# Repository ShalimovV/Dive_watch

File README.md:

# Dive_watch
DIY dive computer project for free diving

KiCAD project - https://github.com/ShalimovV/Dive_watch/tree/main/Hardware/d_watch_v2

Source code are here - https://github.com/ShalimovV/d_watch_v2_wb55

Youtube - https://www.youtube.com/@ShalimovProjects

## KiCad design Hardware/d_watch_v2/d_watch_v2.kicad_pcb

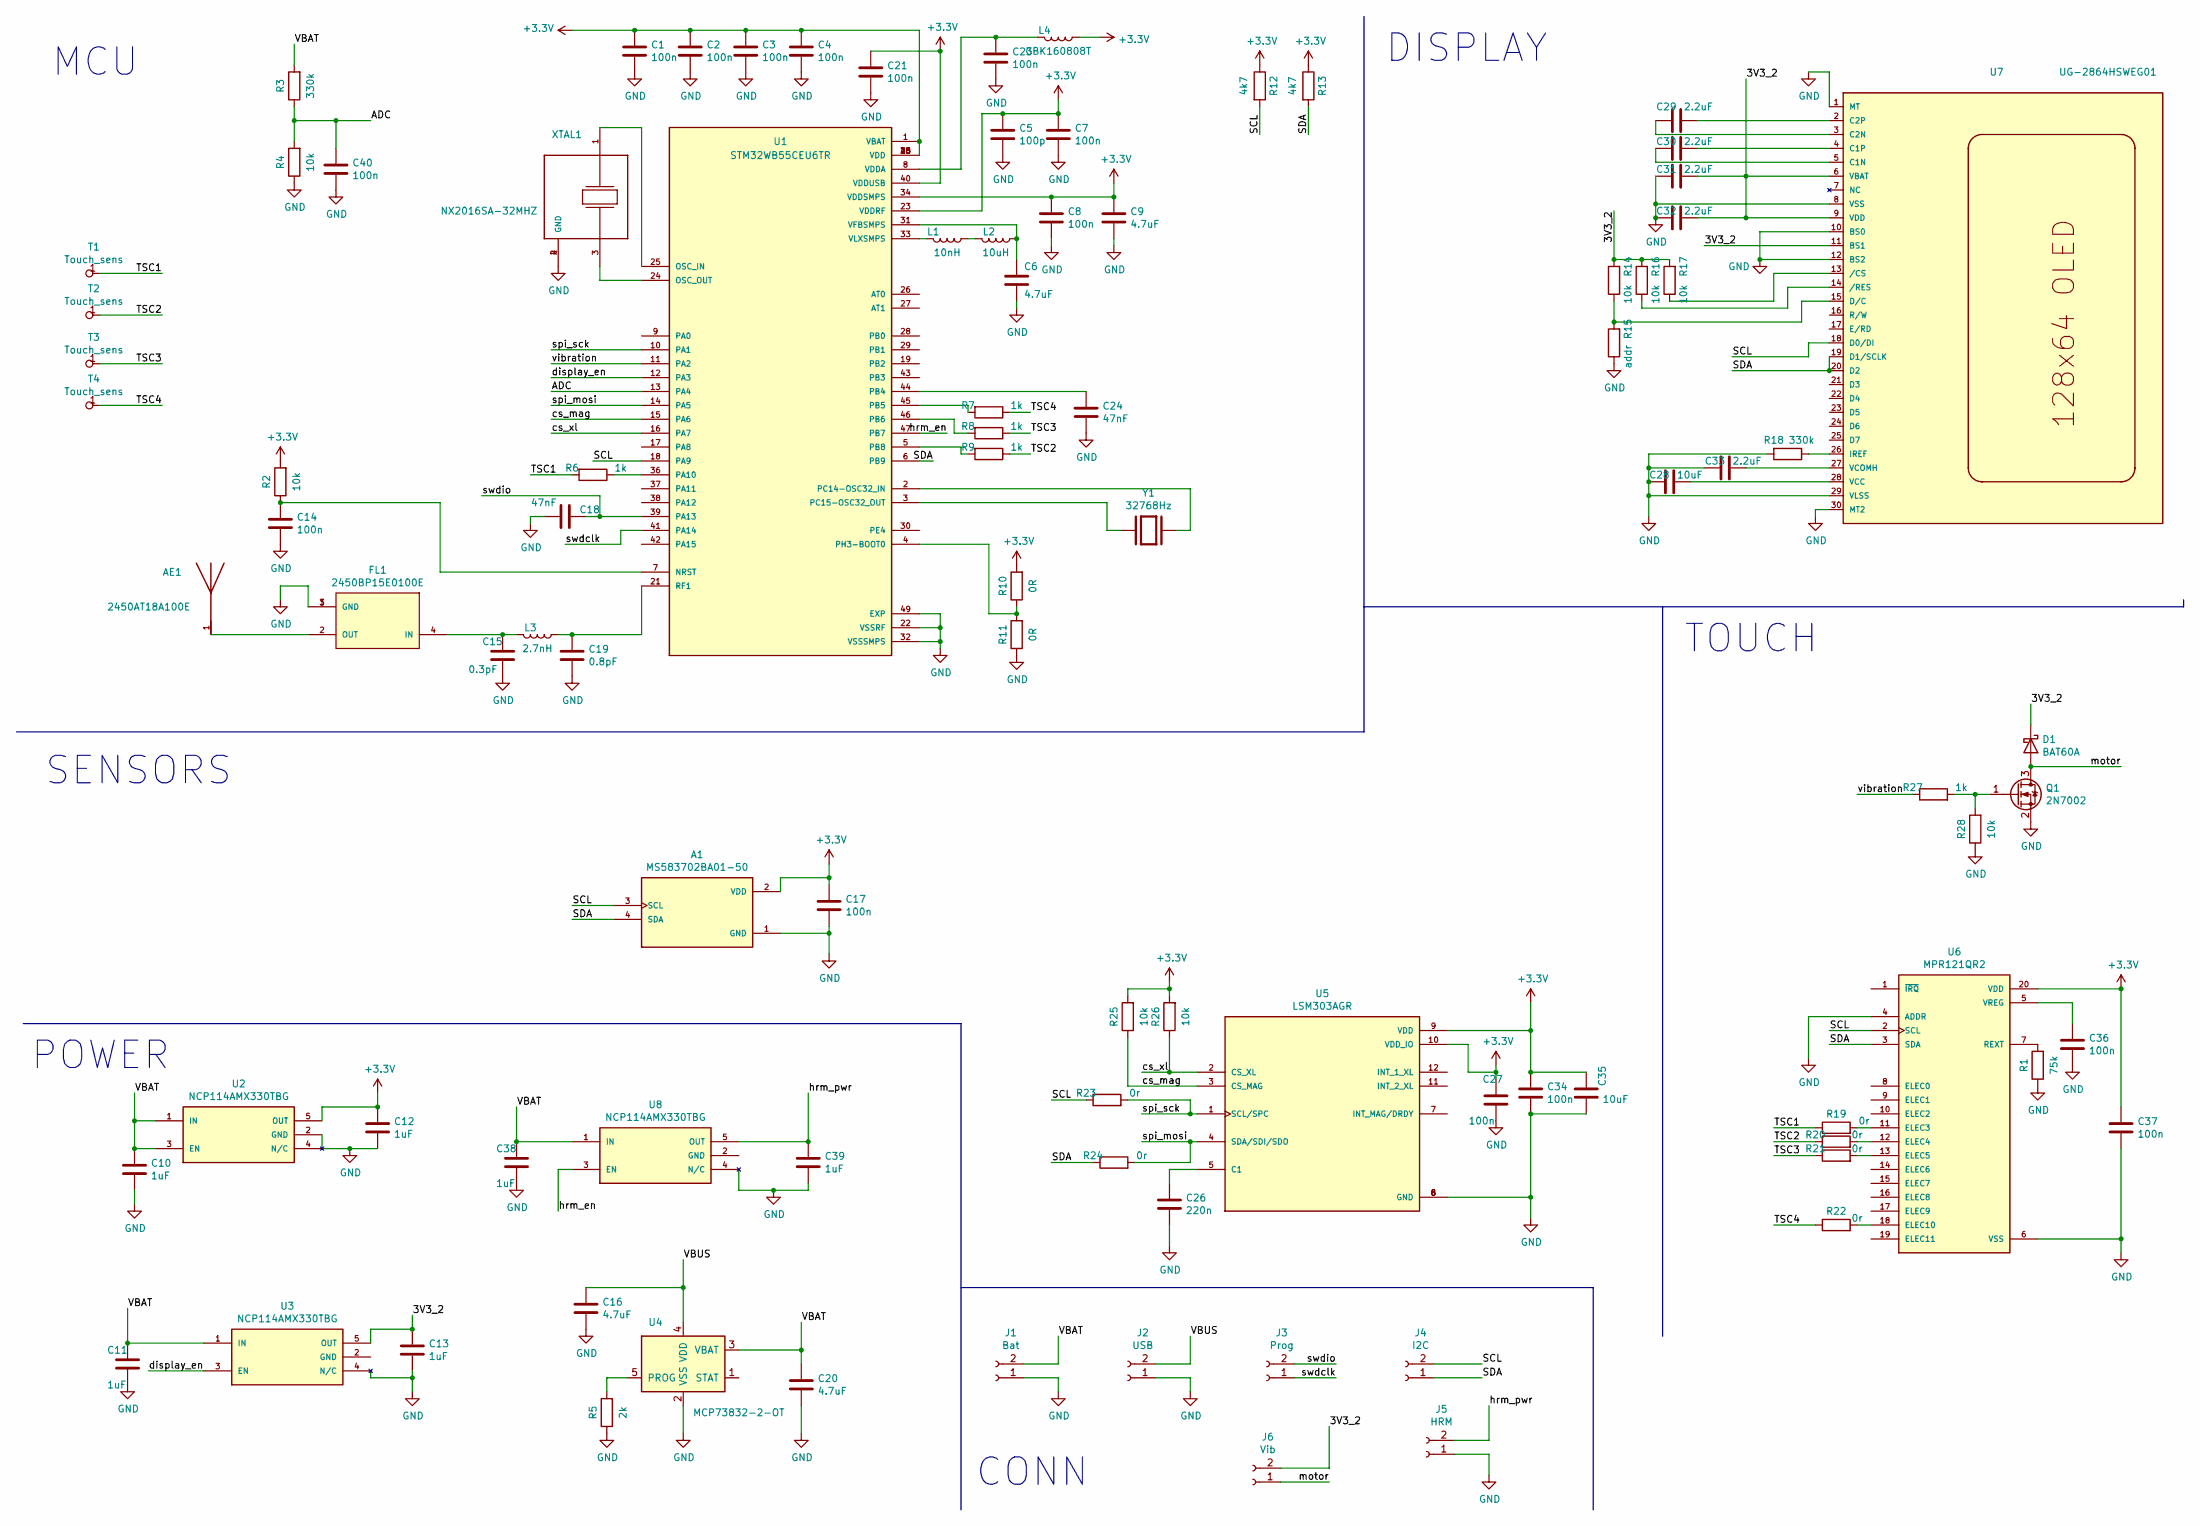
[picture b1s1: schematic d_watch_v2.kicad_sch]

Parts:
A1: MS583702BA01-50; XDCR_MS583702BA01-50
AE1: 2450AT18A100E; ANTC3216X140N; PARTREV 1.3
C1, C2, C3, C4, C7, C8, C14, C17, C21, C23, C27, C34, C36, C37, C40: 100n; C_0603_1608Metric
C5: 100p; C_0603_1608Metric
C6, C9, C16, C20: 4.7uF; C_0603_1608Metric
C10, C11, C12, C13, C38, C39: 1uF; C_0603_1608Metric
C15: 0.3pF; C_0603_1608Metric
C18, C24: 47nF; C_0603_1608Metric
C19: 0.8pF; C_0603_1608Metric
C26: 220n; C_0603_1608Metric
C28, C35: 10uF; C_0603_1608Metric
C29, C30, C31, C32, C33: 2.2uF; C_0603_1608Metric
D1: BAT60A; D_SOD-323
FL1: 2450BP15E0100E; FIL_2450BP15E0100E; PARTREV 1.0
J1: Bat; PinHeader_1x02_P2.54mm_Vertical
J2: USB; PinHeader_1x02_P2.54mm_Vertical
J3: Prog; PinHeader_1x02_P2.54mm_Vertical
J4: I2C; PinHeader_1x02_P2.54mm_Vertical
J5: HRM; PinHeader_1x02_P2.54mm_Vertical
J6: Vib; PinHeader_1x02_P1.00mm_Vertical
L1: 10nH; L_0603_1608Metric
L2: 10uH; L_0603_1608Metric
L3: 2.7nH; L_0603_1608Metric
L4: GBK160808T; L_0603_1608Metric
Q1: 2N7002; SOT-23
R1: 75k; R_0603_1608Metric
R2, R4, R14, R16, R17, R25, R26, R28: 10k; R_0603_1608Metric
R3, R18: 330k; R_0603_1608Metric
R5: 2k; R_0603_1608Metric
R6, R7, R8, R9, R27: 1k; R_0603_1608Metric
R10, R11: 0R; R_0603_1608Metric
R12, R13: 4k7; R_0603_1608Metric
R15: addr; R_0603_1608Metric
R19, R20, R21, R22, R23, R24: 0r; R_0603_1608Metric
T1, T2, T3, T4: Touch_sens; touch_pad
U1: STM32WB55CEU6TR; QFN-48-1EP_7x7mm_P0.5mm_EP5.45x5.45mm; PARTREV 5
U2, U3, U8: NCP114AMX330TBG; SOT-23-5
U4: MCP73832-2-OT; SOT-23-5
U5: LSM303AGR; LGA-12_2x2mm_P0.5mm
U6: MPR121QR2; QFN40P300X300X60-20N
U7: UG-2864HSWEG01; 1X30-0.7MM
XTAL1: NX2016SA-32MHZ; OSCCC200X160X50N; PARTREV N/A
Y1: 32768Hz; XTAL_12.87150; PARTREV 22.06.2021

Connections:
+3V3: A1.2 (VDD), C1.1, C2.1, C3.1, C4.1, C5.1, C7.1, C8.1, C9.1, C12.1, C17.1, C21.1, C27.1, C34.1, C35.1, C37.1, L4.1, R2.2, R10.2, R12.1, R13.1, R25.2, R26.2, U1.1 (VBAT), U1.20 (VDD), U1.23 (VDDRF), U1.34 (VDDSMPS), U1.35 (VDD), U1.40 (VDDUSB), U1.48 (VDD), U2.5 (OUT), U5.9 (VDD), U5.10 (VDD_IO), U6.20 (VDD)
/3V3_2: C13.1, C31.1, C32.1, D1.1 (K), J6.2, R14.2, R16.2, R17.2, U3.5 (OUT), U7.6 (VBAT), U7.9 (VDD), U7.11 (BS1)
/ADC: C40.1, R3.1, R4.2, U1.13 (PA4)
/SCL: A1.3 (SCL), J4.2, R12.2, R23.1, U1.18 (PA9), U6.2 (SCL), U7.18 (D0/DI)
/SDA: A1.4 (SDA), J4.1, R13.2, R24.1, U1.6 (PB9), U6.3 (SDA), U7.19 (D1/SCLK), U7.20 (D2)
/TSC1: R6.2, R19.1, T1.1
/TSC2: R9.1, R20.1, T2.1
/TSC3: R8.1, R21.1, T3.1
/TSC4: R7.1, R22.1, T4.1
/VBAT: C10.1, C11.1, C20.1, C38.1, J1.2, R3.2, U2.1 (IN), U2.3 (EN), U3.1 (IN), U4.3 (VBAT), U8.1 (IN)
/VBUS: C16.1, J2.2, U4.4 (VDD)
/cs_mag: R25.1, U1.15 (PA6), U5.3 (CS_MAG)
/cs_xl: R26.1, U1.16 (PA7), U5.2 (CS_XL)
/display_en: U1.12 (PA3), U3.3 (EN)
/hrm_en: U1.47 (PB7), U8.3 (EN)
/hrm_pwr: C39.1, J5.2, U8.5 (OUT)
/motor: D1.2 (A), J6.1, Q1.3 (D)
/spi_mosi: R24.2, U1.14 (PA5), U5.4 (SDA/SDI/SDO)
/spi_sck: R23.2, U1.10 (PA1), U5.1 (SCL/SPC)
/swdclk: J3.1, U1.41 (PA14)
/swdio: C18.1, J3.2, U1.39 (PA13)
/vibration: R27.1, U1.11 (PA2)
GND: A1.1 (GND), C1.2, C2.2, C3.2, C4.2, C5.2, C6.2, C7.2, C8.2, C9.2, C10.2, C11.2, C12.2, C13.2, C14.2, C15.2, C16.2, C17.2, C18.2, C19.2, C20.2, C21.2, C23.2, C24.2, C26.2, C27.2, C28.2, C31.2, C32.2, C33.2, C34.2, C35.2, C36.2, C37.2, C38.2, C39.2, C40.2, FL1.1 (GND), FL1.3 (GND), J1.1, J2.1, J5.1, Q1.2 (S), R1.1, R4.1, R5.1, R11.1, R15.1, R18.2, R28.1, U1.22 (VSSRF), U1.32 (VSSSMPS), U1.49 (EXP), U2.2 (GND), U2.4 (N/C), U3.4 (N/C), U4.2 (VSS), U5.6 (GND), U5.8 (GND), U6.4 (ADDR), U6.6 (VSS), U7.1 (MT), U7.8 (VSS), U7.10 (BS0), U7.12 (BS2), U7.29 (VLSS), U7.30 (MT2), U8.4 (N/C), XTAL1.2 (GND), XTAL1.4 (GND); also elsewhere on the board
unnamed: AE1.1, FL1.2 (OUT)
unnamed: C6.1, L2.1, U1.31 (VFBSMPS)
unnamed: C14.1, R2.1, U1.7 (NRST)
unnamed: C15.1, FL1.4 (IN), L3.2
unnamed: C19.1, L3.1, U1.21 (RF1)
unnamed 28: U1.3 (PC15-OSC32_OUT), Y1.1; also elsewhere on the board
unnamed: C23.1, L4.2, U1.8 (VDDA)
unnamed: C24.1, U1.44 (PB4)
unnamed 31: U1.2 (PC14-OSC32_IN), Y1.2; also elsewhere on the board
unnamed: C26.1, U5.5 (C1)
unnamed: C28.1, U7.28 (VCC)
unnamed: C29.1, U7.2 (C2P)
unnamed: C29.2, U7.3 (C2N)
unnamed: C30.1, U7.4 (C1P)
unnamed: C30.2, U7.5 (C1N)
unnamed: C33.1, U7.27 (VCOMH)
unnamed: C36.1, U6.5 (VREG)
unnamed: L1.1, L2.2
unnamed: L1.2, U1.33 (VLXSMPS)
unnamed: Q1.1 (G), R27.2, R28.2
unnamed: R1.2, U6.7 (REXT)
unnamed: R5.2, U4.5 (PROG)
unnamed: R6.1, U1.36 (PA10)
unnamed: R7.2, U1.45 (PB5)
unnamed: R8.2, U1.46 (PB6)
unnamed: R9.2, U1.5 (PB8)
unnamed: R10.1, R11.2, U1.4 (PH3-BOOT0)
unnamed: R14.1, R15.2, U7.15 (D/C)
unnamed: R16.1, U7.14 (/RES)
unnamed: R17.1, U7.13 (/CS)
unnamed: R18.1, U7.26 (IREF)
unnamed: R19.2, U6.11 (ELEC3)
unnamed: R20.2, U6.12 (ELEC4)
unnamed: R21.2, U6.13 (ELEC5)
unnamed: R22.2, U6.18 (ELEC10)
unnamed: U1.24 (OSC_OUT), XTAL1.3
unnamed: U1.25 (OSC_IN), XTAL1.1

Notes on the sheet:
SENSORS
DISPLAY
CONN
POWER
MCU
TOUCH

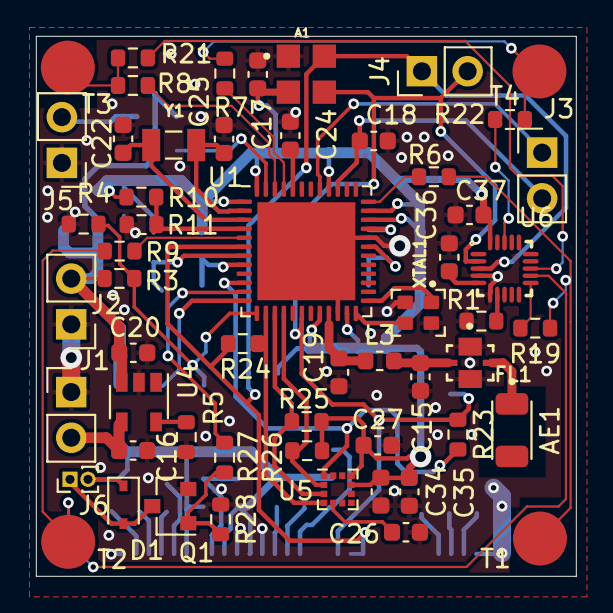
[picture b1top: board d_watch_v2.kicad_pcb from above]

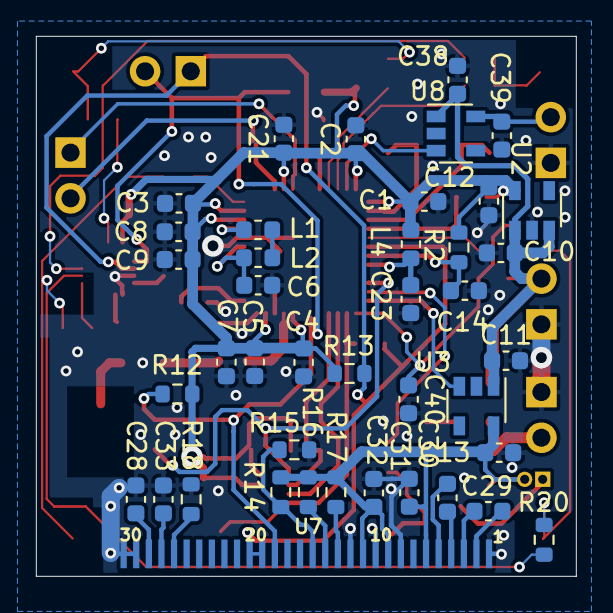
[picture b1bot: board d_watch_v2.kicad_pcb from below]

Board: 2 copper layers, 30.0 x 30.0 mm, 97 parts (41 on the bottom side), 60 nets.

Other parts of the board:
C22, C25: 15pF; C_0603_1608Metric

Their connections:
GND: C22.2, C25.2; also elsewhere on the board
unnamed 28: C22.1; also elsewhere on the board
unnamed 31: C25.1; also elsewhere on the board
